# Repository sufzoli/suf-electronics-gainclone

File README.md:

# suf-electronics-gainclone
My GainCard amplifier implementation

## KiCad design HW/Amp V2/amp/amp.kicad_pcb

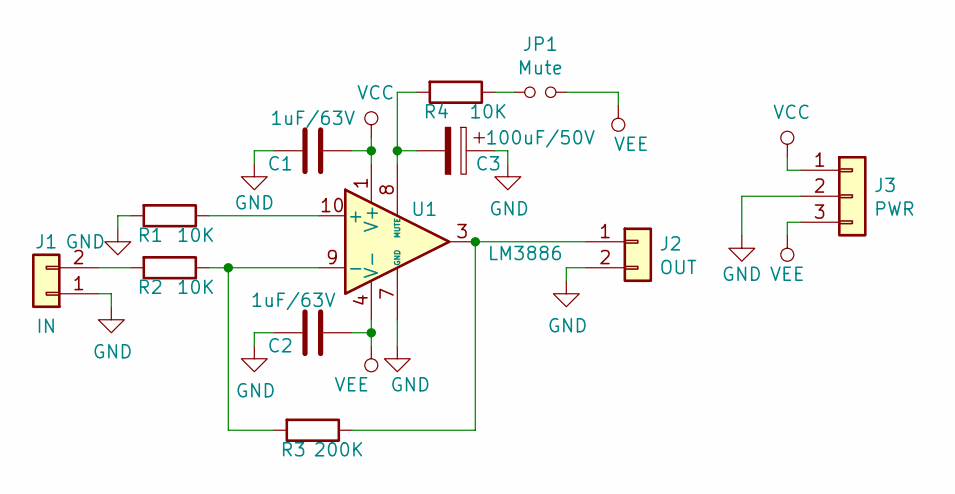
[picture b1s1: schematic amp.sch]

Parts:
C1, C2: 1uF/63V; C_Rect_L7.2mm_W2.5mm_P5.00mm_FKS2_FKP2_MKS2_MKP2
C3: 100uF/50V; CP_Radial_D8.0mm_P3.50mm
J1: IN; JST_EH_B02B-EH-A_02x2.50mm_Straight
J2: OUT; CONN_NCW396-02S
J3: PWR; CONN_NCW396-03S
JP1: Mute; Pin_Header_Straight_1x02_Pitch2.54mm
R1, R2, R4: 10K; R_Axial_DIN0207_L6.3mm_D2.5mm_P10.16mm_Horizontal
R3: 200K; R_Axial_DIN0207_L6.3mm_D2.5mm_P10.16mm_Horizontal
U1: LM3886; TO-220-11_Vertical_StaggeredType1

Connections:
GND: C1.2, C2.2, C3.1, J1.1, J2.2, J3.2, R1.2, U1.7 (GND)
unnamed: C3.2, R4.2, U1.8 (MUTE)
unnamed: J1.2, R2.2
unnamed: J2.1, R3.1, U1.3
unnamed: JP1.1, R4.1
unnamed: R1.1, U1.10 (+)
unnamed: R2.1, R3.2, U1.9 (-)
VCC: C1.1, J3.1, U1.1 (V+), U1.5 (V+)
VEE: C2.1, J3.3, JP1.2, U1.4 (V-)

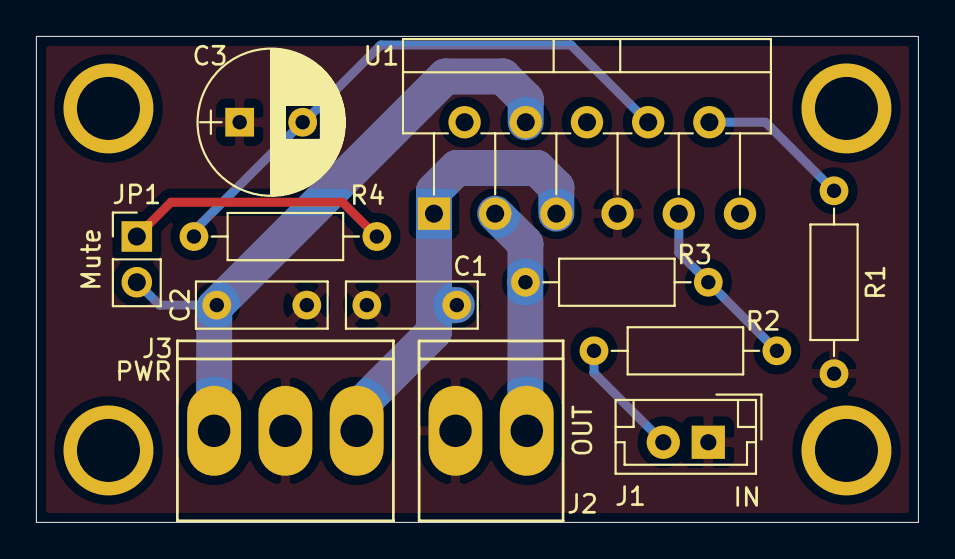
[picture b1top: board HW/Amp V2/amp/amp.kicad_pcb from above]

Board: 2 copper layers, 49.0 x 27.0 mm, 16 parts (0 on the bottom side), 9 nets.

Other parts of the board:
MNT_HOLE_3.5S, MNT_HOLE_3.5S#2, MNT_HOLE_3.5S#3, MNT_HOLE_3.5S#4: Val**; MNT_HOLE_3.5S

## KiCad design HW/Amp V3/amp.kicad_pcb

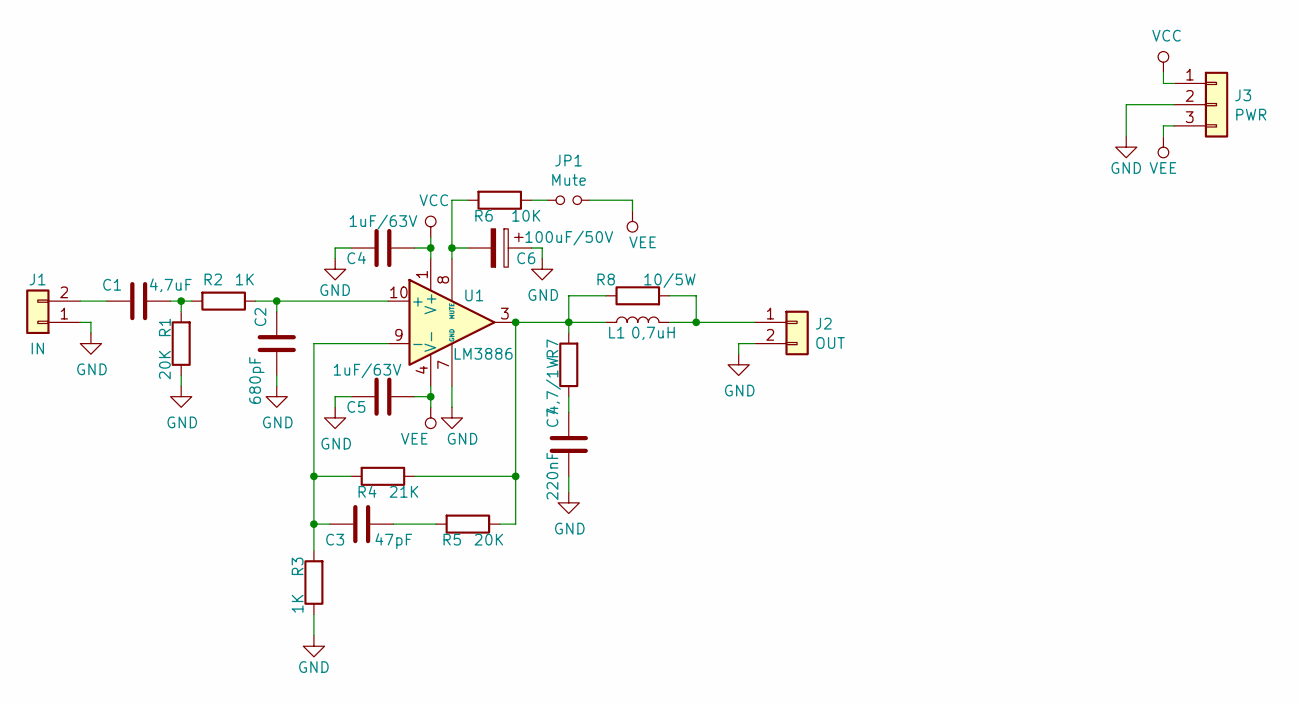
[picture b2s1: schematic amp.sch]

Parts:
C1: 4,7uF; C_Axial_L32mm_D20mm_P37.5mm_Horizontal
C2: 680pF; C_Disc_D3.0mm_W1.6mm_P2.50mm
C3: 47pF; C_Disc_D3.0mm_W1.6mm_P2.50mm
C4, C5: 1uF/63V; C_Rect_L7.2mm_W2.5mm_P5.00mm_FKS2_FKP2_MKS2_MKP2
C6: 100uF/50V; CP_Radial_D8.0mm_P3.50mm
C7: 220nF; C_Axial_L15mm_D10mm_P20mm_Horizontal
J1: IN; JST_EH_B02B-EH-A_02x2.50mm_Straight
J2: OUT; CONN_NCW396-02S
J3: PWR; CONN_NCW396-03S
JP1: Mute; Pin_Header_Straight_1x02_Pitch2.54mm
L1: 0,7uH; L_D16_d2_L20_Axial_AirCore
R1, R5: 20K; R_Axial_DIN0207_L6.3mm_D2.5mm_P10.16mm_Horizontal
R2, R3: 1K; R_Axial_DIN0207_L6.3mm_D2.5mm_P10.16mm_Horizontal
R4: 21K; R_Axial_DIN0207_L6.3mm_D2.5mm_P10.16mm_Horizontal
R6: 10K; R_Axial_DIN0207_L6.3mm_D2.5mm_P10.16mm_Horizontal
R7: 4,7/1W; R_Axial_DIN0309_L9.0mm_D3.2mm_P15.24mm_Horizontal
R8: 10/5W; R_Axial_DIN0617_L17.0mm_D6.0mm_P25.40mm_Horizontal
U1: LM3886; TO-220-11_Vertical_StaggeredType1

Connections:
GND: C2.1, C4.2, C5.2, C6.1, C7.1, J1.1, J2.2, J3.2, R1.1, R3.1, U1.7 (GND)
unnamed: C1.1, R1.2, R2.2
unnamed: C1.2, J1.2
unnamed: C2.2, R2.1, U1.10 (+)
unnamed: C3.1, R5.2
unnamed: C3.2, R3.2, R4.2, U1.9 (-)
unnamed: C6.2, R6.2, U1.8 (MUTE)
unnamed: C7.2, R7.1
unnamed: J2.1, L1.2, R8.2
unnamed: JP1.1, R6.1
unnamed: L1.1, R4.1, R5.1, R7.2, R8.1, U1.3
VCC: C4.1, J3.1, U1.1 (V+), U1.5 (V+)
VEE: C5.1, J3.3, JP1.2, U1.4 (V-)

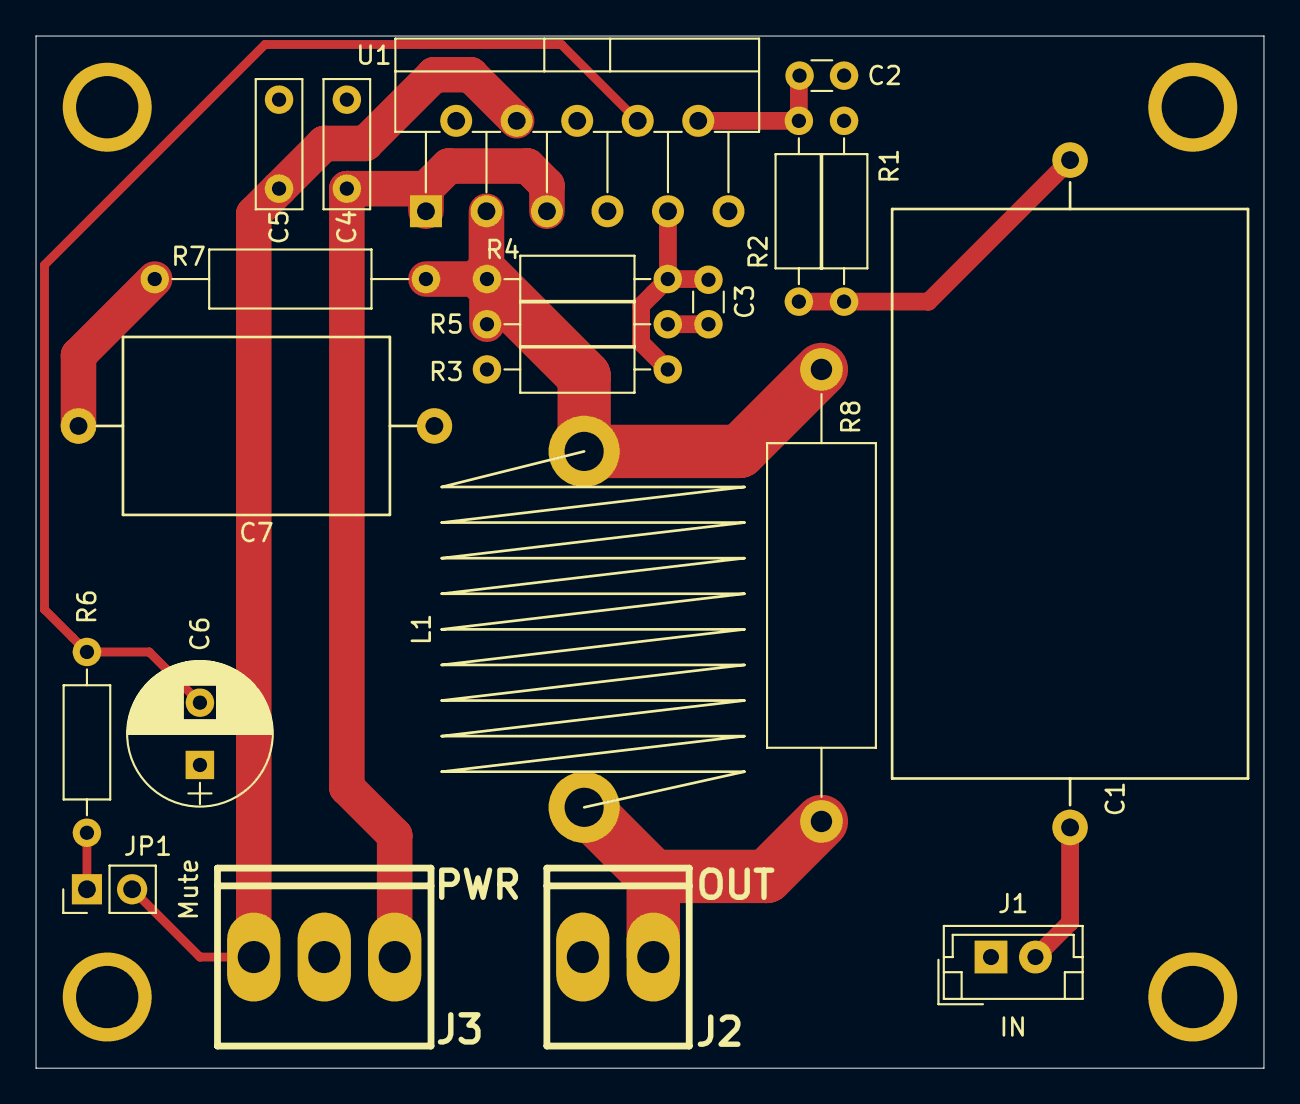
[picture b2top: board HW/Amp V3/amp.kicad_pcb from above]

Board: 2 copper layers, 69.0 x 58.0 mm, 25 parts (0 on the bottom side), 13 nets.

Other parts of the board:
MNT_HOLE_3.5S, MNT_HOLE_3.5S#2, MNT_HOLE_3.5S#3, MNT_HOLE_3.5S#4: Val**; MNT_HOLE_3.5S

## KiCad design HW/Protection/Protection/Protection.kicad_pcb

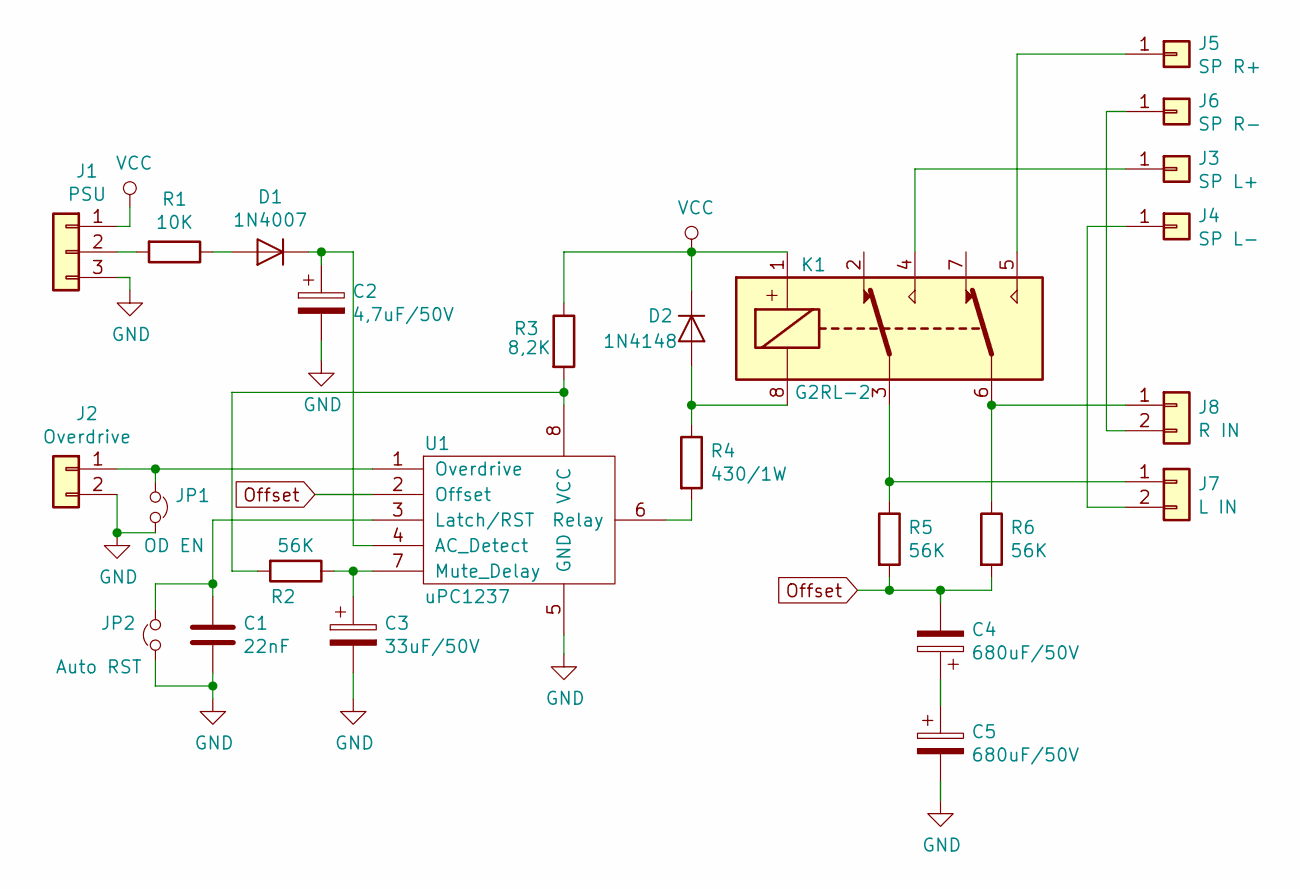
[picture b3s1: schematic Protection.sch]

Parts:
C1: 22nF; C_Disc_D3.0mm_W1.6mm_P2.50mm
C2: 4,7uF/50V; CP_Radial_D4.0mm_P1.50mm
C3: 33uF/50V; CP_Radial_D8.0mm_P3.50mm
C4, C5: 680uF/50V; CP_Radial_D13.0mm_P5.00mm
D1: 1N4007; D_DO-41_SOD81_P10.16mm_Horizontal
D2: 1N4148; D_DO-35_SOD27_P7.62mm_Horizontal
J1: PSU; JST_EH_B03B-EH-A_03x2.50mm_Straight
J2: Overdrive; JST_EH_B02B-EH-A_02x2.50mm_Straight
J3: SP L+; SPEAKER_8mm
J4: SP L-; SPEAKER_8mm
J5: SP R+; SPEAKER_8mm
J6: SP R-; SPEAKER_8mm
J7: L IN; CONN_NCW396-02S
J8: R IN; CONN_NCW396-02S
JP1: OD EN; Pin_Header_Straight_1x02_Pitch2.54mm
JP2: Auto RST; Pin_Header_Straight_1x02_Pitch2.54mm
K1: G2RL-2; Relay_DPDT_Panasonic_JW2
R1: 10K; R_Axial_DIN0207_L6.3mm_D2.5mm_P10.16mm_Horizontal
R2, R5, R6: 56K; R_Axial_DIN0207_L6.3mm_D2.5mm_P10.16mm_Horizontal
R3: 8,2K; R_Axial_DIN0207_L6.3mm_D2.5mm_P10.16mm_Horizontal
R4: 430/1W; R_Axial_DIN0309_L9.0mm_D3.2mm_P15.24mm_Horizontal
U1: uPC1237; SIP-8_19x3mm_Pitch2.54mm

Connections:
GND: C1.2, C2.2, C3.2, C5.2, J1.3, J2.2, JP1.2, JP2.2, U1.5 (GND)
unnamed: C1.1, JP2.1, U1.3 (Latch/RST)
unnamed: C2.1, D1.1 (K), U1.4 (AC_Detect)
unnamed: C3.1, R2.1, U1.7 (Mute_Delay)
unnamed: C4.1, C5.1
unnamed: D1.2 (A), R1.1
unnamed: D2.2 (A), K1.8, R4.1
unnamed: J1.2, R1.2
unnamed: J2.1, JP1.1, U1.1 (Overdrive)
unnamed: J3.1, K1.4
unnamed: J4.1, J7.2
unnamed: J5.1, K1.5
unnamed: J6.1, J8.2
unnamed: J7.1, K1.3, R5.1
unnamed: J8.1, K1.6, R6.1
unnamed: R2.2, R3.2, U1.8 (VCC)
unnamed: R4.2, U1.6 (Relay)
Offset: C4.2, R5.2, R6.2, U1.2 (Offset)
VCC: D2.1 (K), J1.1, K1.1, R3.1

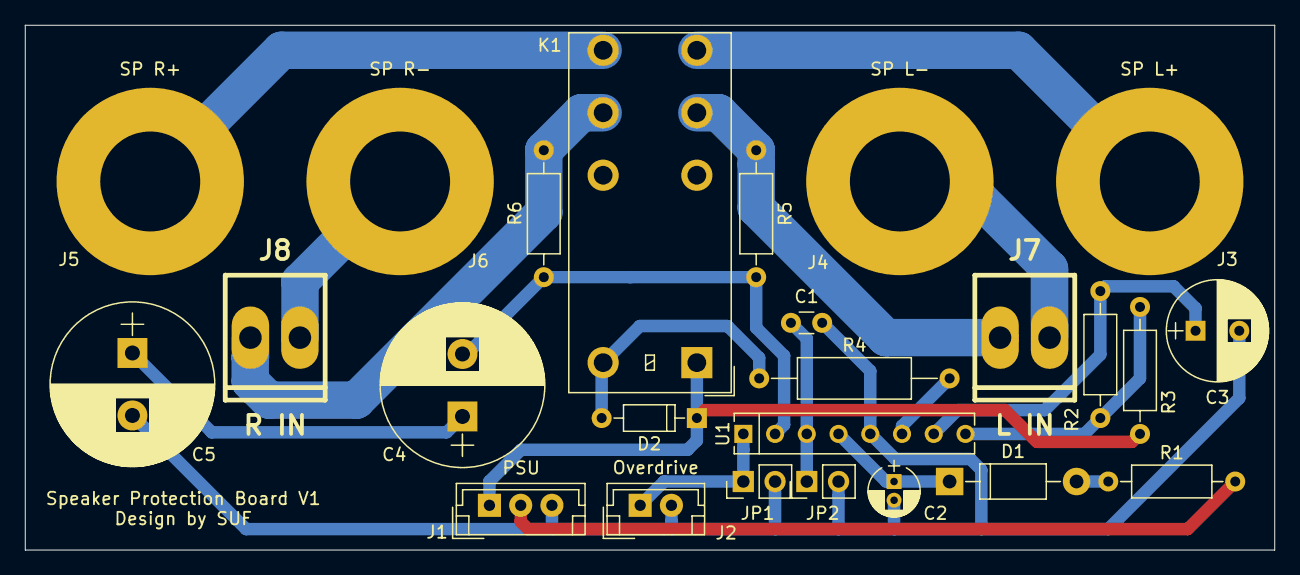
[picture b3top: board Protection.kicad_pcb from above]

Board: 2 copper layers, 100.0 x 42.0 mm, 25 parts (0 on the bottom side), 19 nets.

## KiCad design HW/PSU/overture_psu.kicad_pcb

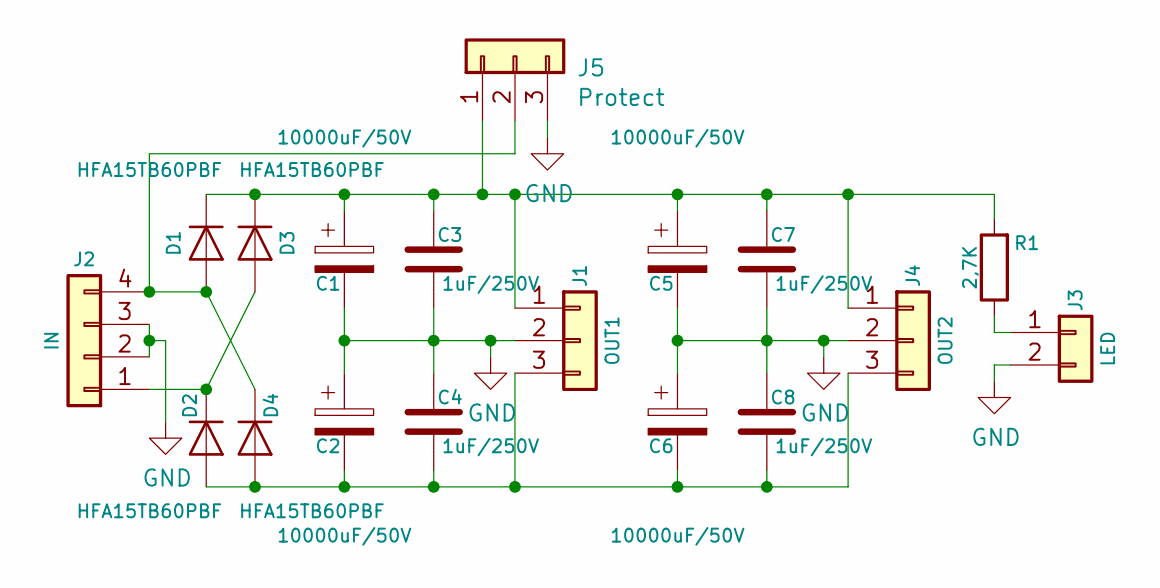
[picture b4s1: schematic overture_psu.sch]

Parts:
C1, C2, C5, C6: 10000uF/50V; CP_Radial_D35.0mm_P10.00mm_SnapIn
C3, C4, C7, C8: 1uF/250V; C_Rect_L26.5mm_W11.5mm_P22.50mm_MKS4
D1, D2, D3, D4: HFA15TB60PBF; TO-220-2_Vertical
J1: OUT1; CONN_NCW396-03S
J2: IN; TerminalBlock_bornier-4_P5.08mm
J3: LED; CONN_NCW254-02S
J4: OUT2; CONN_NCW396-03S
J5: Protect; JST_EH_B03B-EH-A_03x2.50mm_Straight
R1: 2,7K; R_Axial_DIN0207_L6.3mm_D2.5mm_P10.16mm_Horizontal

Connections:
GND: C1.2, C2.1, C3.1, C4.2, C5.2, C6.1, C7.1, C8.2, J1.2, J2.2, J2.3, J3.2, J4.2, J5.3
unnamed: C1.1, C3.2, C5.1, C7.2, D1.1 (K), D3.1 (K), J1.1, J4.1, J5.1, R1.2
unnamed: C2.2, C4.1, C6.2, C8.1, D2.2 (A), D4.2 (A), J1.3, J4.3
unnamed: D1.2 (A), D4.1 (K), J2.4, J5.2
unnamed: D2.1 (K), D3.2 (A), J2.1
unnamed: J3.1, R1.1

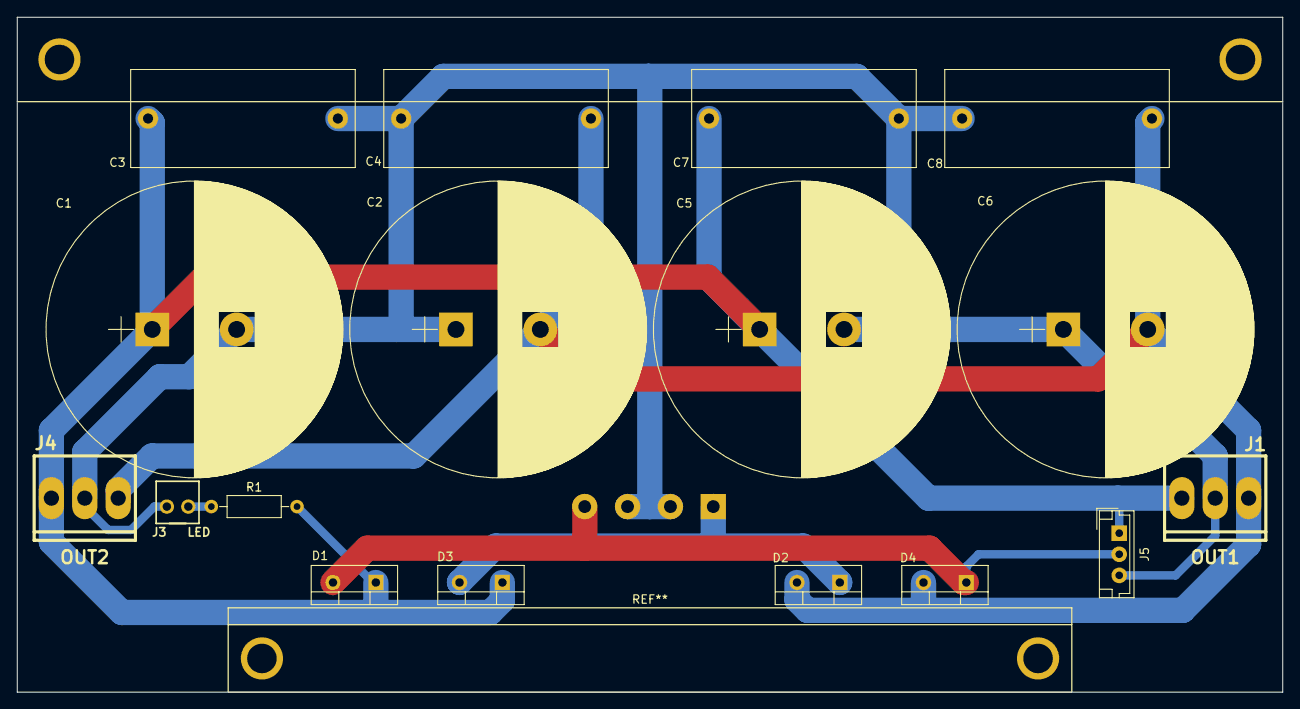
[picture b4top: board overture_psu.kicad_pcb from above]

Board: 2 copper layers, 150.0 x 80.0 mm, 22 parts (1 on the bottom side), 6 nets.

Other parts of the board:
MNT_HOLE_3.5S, MNT_HOLE_3.5S#2, MNT_HOLE_3.5S#3, MNT_HOLE_3.5S#4: Val**; MNT_HOLE_3.5S

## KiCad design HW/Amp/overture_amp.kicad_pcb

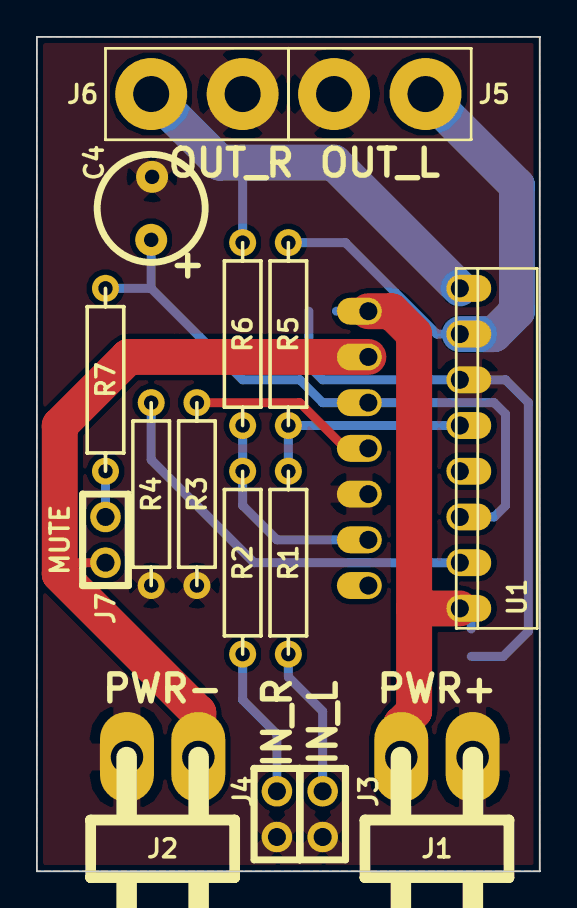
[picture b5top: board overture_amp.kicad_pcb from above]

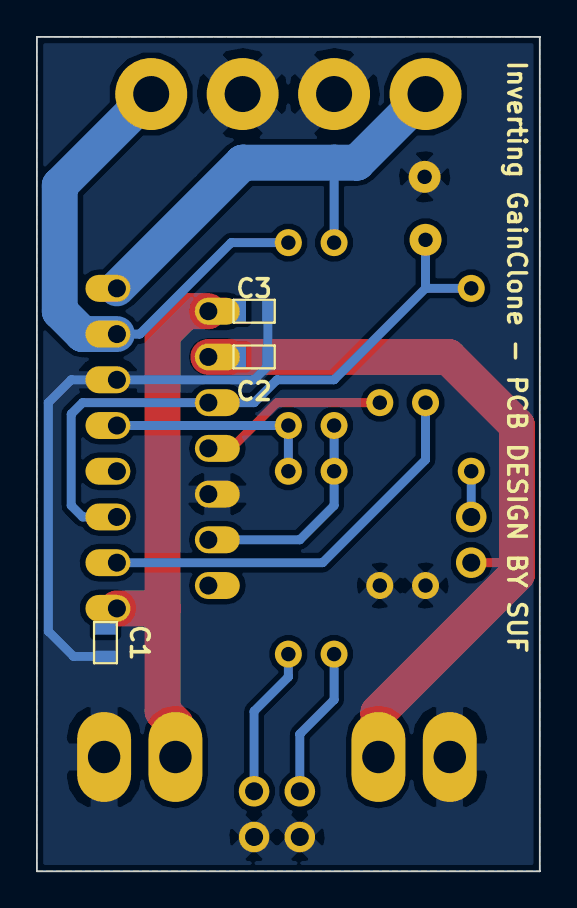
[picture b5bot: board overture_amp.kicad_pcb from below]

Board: 2 copper layers, 27.9 x 46.4 mm, 19 parts (3 on the bottom side), 13 nets.

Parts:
C1, C2, C3: 100nF; SM0603
C4: 33uF/50V; C1,5P_D2,5
J1: PWR+; CONN_NCW396-02R
J2: PWR-; CONN_NCW396-02R
J3: IN_L; HDR-2
J4: IN_R; HDR-2
J5: OUT_L; HDR-2-5,08
J6: OUT_R; HDR-2-5,08
J7: MUTE; HDR-2
R1, R2, R3, R4: 10K; R4
R5, R6: 220K; R4
R7: 12K; R4
U1: LM4766; TO220-15

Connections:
GND: C1.2, C2.1, C3.2, C4.2, J1.1, J2.2, J3.1, J4.1, J5.2, J6.2, R3.2, R4.2, U1.5, U1.10
unnamed: R2.1, R6.2, U1.12
unnamed: R4.1, U1.13
unnamed: J4.2, R2.2
unnamed: J6.1, R6.1, U1.1
unnamed: J7.1, R7.2
unnamed: C4.1, R7.1, U1.6, U1.11
unnamed: J3.2, R1.2
unnamed: J5.1, R5.1, U1.3
unnamed: R3.1, U1.8
unnamed: R1.1, R5.2, U1.7
VCC: C1.1, C3.1, J1.2, U1.2, U1.15
VEE: C2.2, J2.1, J7.2, U1.4

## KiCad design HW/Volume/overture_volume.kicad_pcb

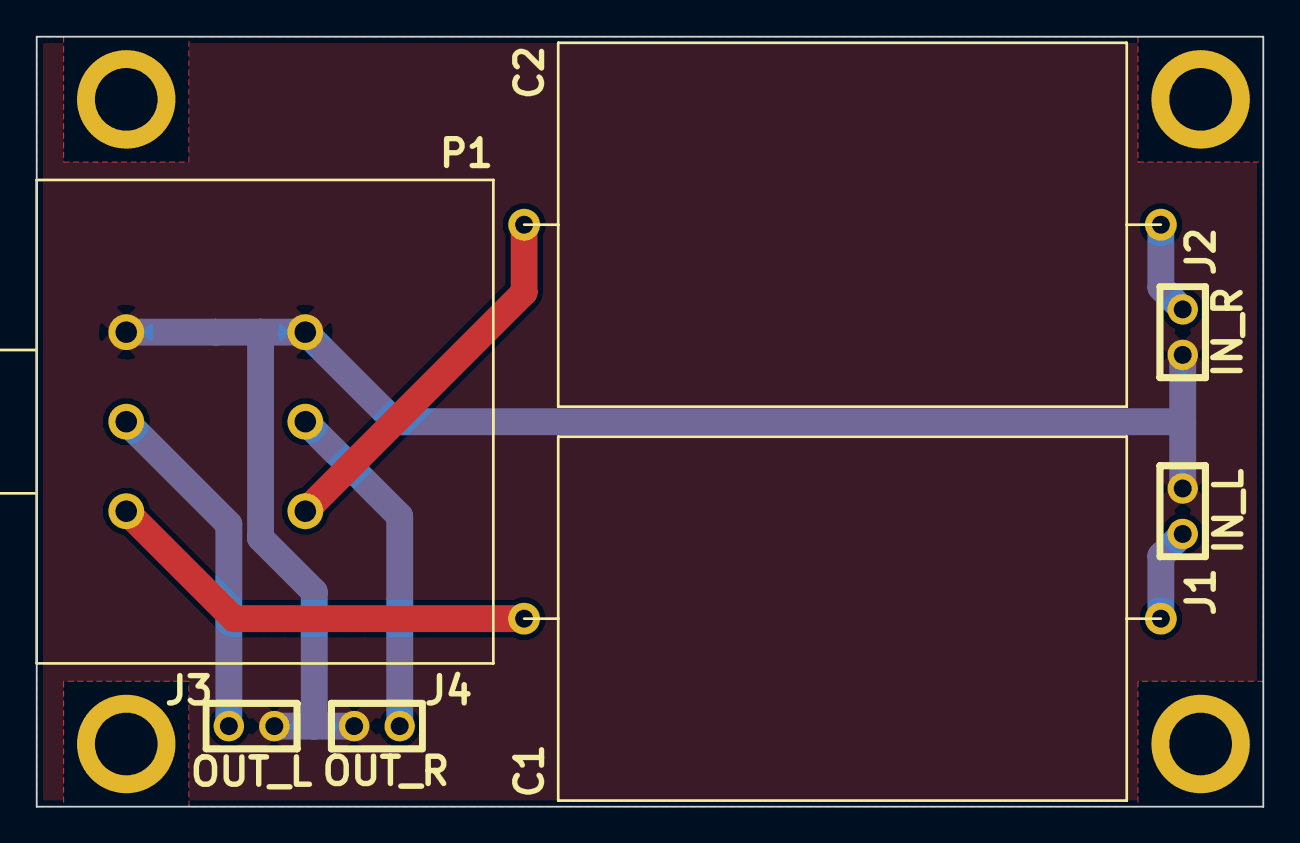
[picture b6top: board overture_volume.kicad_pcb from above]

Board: 2 copper layers, 68.5 x 43.0 mm, 11 parts (0 on the bottom side), 7 nets.

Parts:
C1, C2: 4,7uF; C14_12.5X8
J1: IN_L; HDR-2
J2: IN_R; HDR-2
J3: OUT_L; HDR-2
J4: OUT_R; HDR-2
MNT_HOLE_3.5, MNT_HOLE_3.5#2, MNT_HOLE_3.5#3, MNT_HOLE_3.5#4: MNT_HOLE_3.5
P1: 50K Log; RK27112

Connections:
GND: J1.2, J2.2, J3.2, J4.2, P1.1, P1.4
unnamed: C1.1, J1.1
unnamed: C1.2, P1.3
unnamed: J3.1, P1.2
unnamed: C2.1, J2.1
unnamed: C2.2, P1.6
unnamed: J4.1, P1.5

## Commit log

2015-07-15 Initial Commit - Design transferred to GitHub
2015-07-18 Updated to new KiCAD, Capacitor hole size corrected.
2015-07-19 Mounting holes for volume control and amplifier added to the base plate
2020-01-04 Add V3 (Actually built)
2021-03-20 Add gitignore
